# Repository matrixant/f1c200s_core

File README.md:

#f1c200s_core

> 已打板点灯验证，没有测试过稳定性，谨慎应用。

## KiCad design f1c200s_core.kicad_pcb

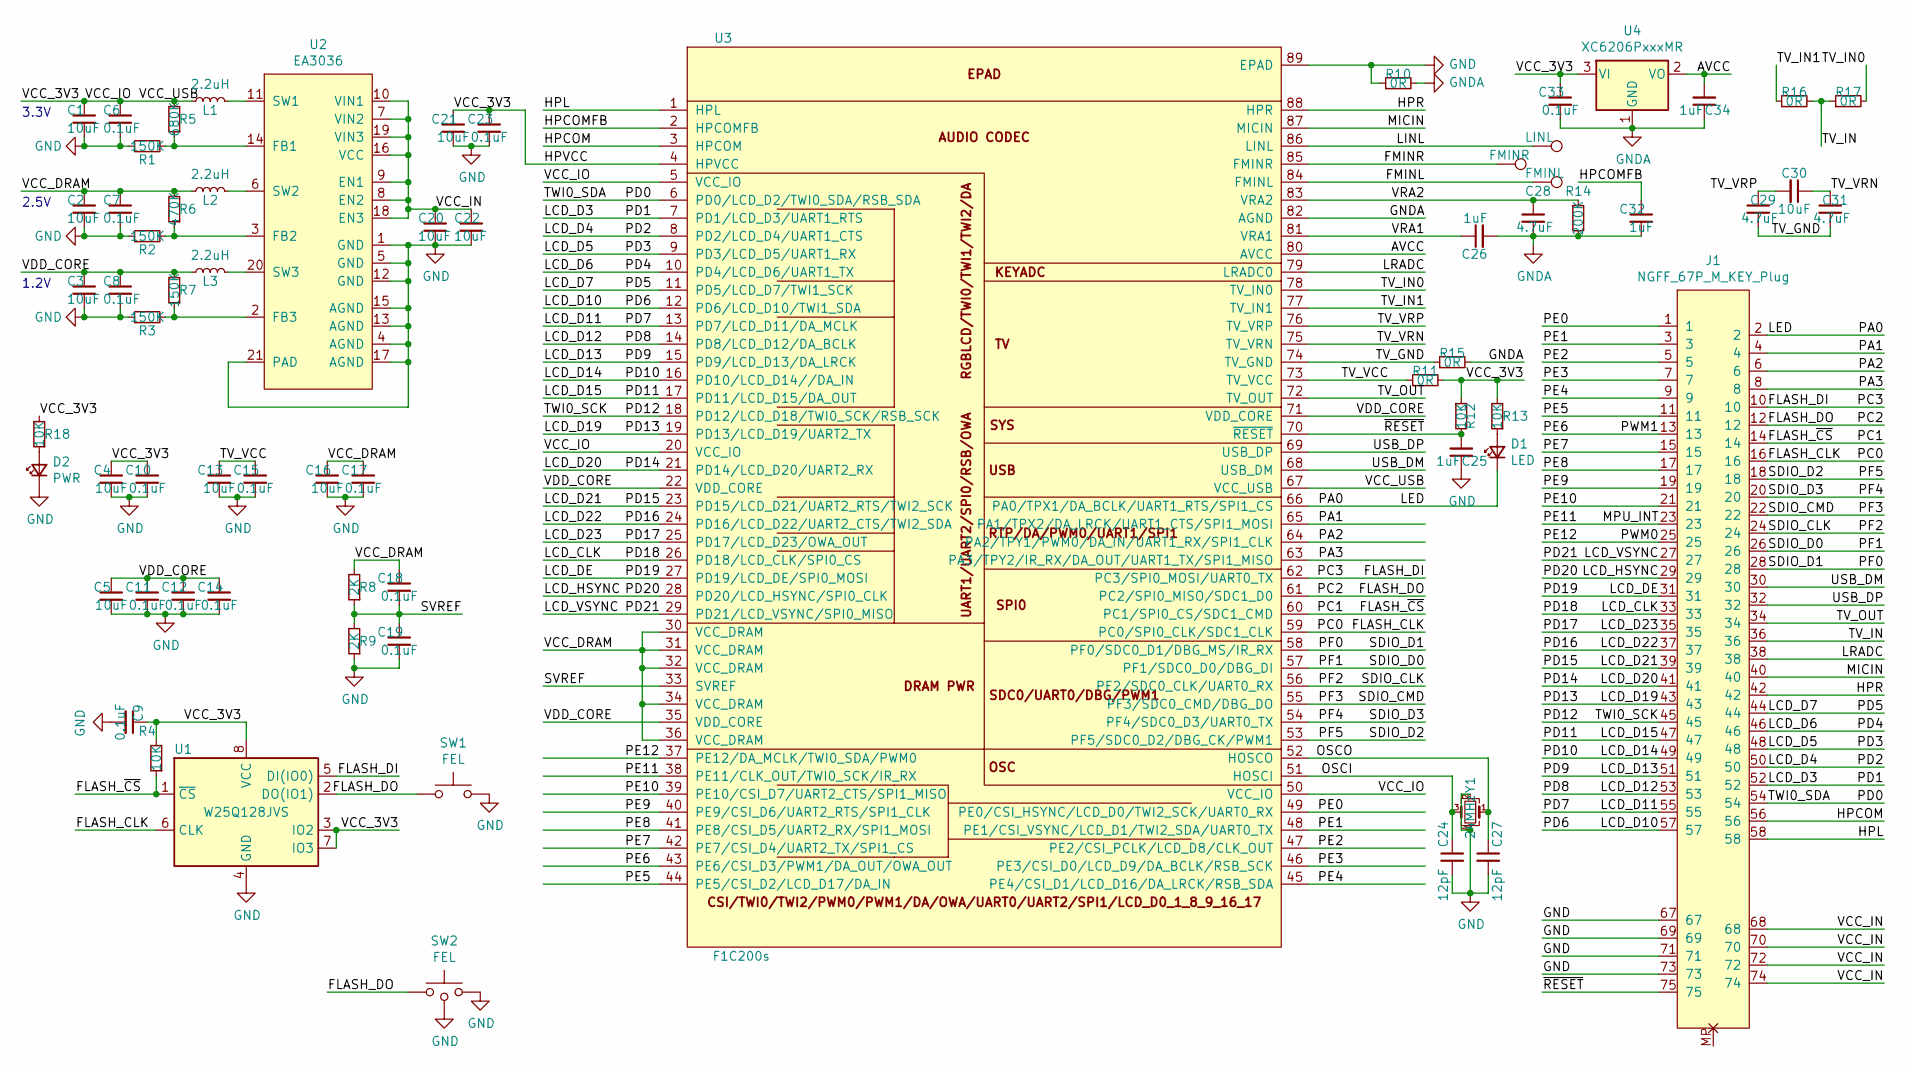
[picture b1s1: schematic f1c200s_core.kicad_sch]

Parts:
C1, C2, C3, C4, C5, C13, C16, C20, C21, C22, C30: 10uF; C_0402_1005Metric
C6, C7, C8, C9, C10, C11, C12, C14, C15, C17, C18, C19, C23, C33: 0.1uF; C_0402_1005Metric
C24, C27: 12pF; C_0402_1005Metric
C25, C26, C32, C34: 1uF; C_0402_1005Metric
C28, C29, C31: 4.7uF; C_0402_1005Metric
D1: LED; LED_0603_1608Metric
D2: PWR; LED_0603_1608Metric
J1: NGFF_67P_M_KEY_Plug; NGFF_2230_67P_P0.5_M_KEY_Plug
L1, L2, L3: 2.2uH; L_1008_2520Metric
R1, R2, R3, R7: 150K; R_0402_1005Metric
R4, R12, R13, R18: 10K; R_0402_1005Metric
R5: 680K; R_0402_1005Metric
R6: 470K; R_0402_1005Metric
R8, R9: 2K; R_0402_1005Metric
R10, R11, R15, R16, R17: 0R; R_0402_1005Metric
R14: 200K; R_0402_1005Metric
SW1: FEL; Key_Push_3.5x5x1.5_Side_4P
SW2: FEL; Key_Push_2x4x3.5_Side_4P
TP1: FMINR; TestPoint_Pad_D1.0mm
TP2: LINL; TestPoint_Pad_D1.0mm
TP3: FMINL; TestPoint_Pad_D1.0mm
U1: W25Q128JVS; WSON-8_8x6mm
U2: EA3036; QFN-20_EP_3x3_Pitch0.4mm_ThermalVias
U3: F1C200s; QFN-88_EP_10x10_Pitch0.4mm_Handsoldering
U4: XC6206PxxxMR; SOT-23
Y1: 24MHz; Crystal_SMD_3225-4Pin_3.2x2.5mm

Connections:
/AVCC: C34.2, U3.80 (AVCC), U4.2 (VO)
/FLASH_CLK: J1.16, U1.6 (CLK), U3.59 (PC0/SPI0_CLK/SDC1_CLK)
/FLASH_DI: J1.10, U1.5 (DI(IO0)), U3.62 (PC3/SPI0_MOSI/UART0_TX)
/FLASH_DO: J1.12, SW1.2, SW2.2, U1.2 (DO(IO1)), U3.61 (PC2/SPI0_MISO/SDC1_D0)
/FLASH_~CS: J1.14, R4.1, U1.1 (~CS), U3.60 (PC1/SPI0_CS/SDC1_CMD)
/FMINL: TP3.1, U3.84 (FMINL)
/FMINR: TP1.1, U3.85 (FMINR)
/HPCOM: J1.56, U3.3 (HPCOM)
/HPCOMFB: C32.1, U3.2 (HPCOMFB)
/HPL: J1.58, U3.1 (HPL)
/HPR: J1.42, U3.88 (HPR)
/HPVCC: C1.1, C4.1, C6.1, C9.1, C10.1, C21.1, C23.1, C33.1, L1.1, R4.2, R5.2, R11.2, R12.1, R13.2, R18.2, U1.3 (IO2), U1.7 (IO3), U1.8 (VCC), U3.4 (HPVCC), U3.5 (VCC_IO), U3.20 (VCC_IO), U3.50 (VCC_IO), U3.67 (VCC_USB), U4.3 (VI)
/LCD_CLK: J1.33, U3.26 (PD18/LCD_CLK/SPI0_CS)
/LCD_D3: J1.52, U3.7 (PD1/LCD_D3/UART1_RTS)
/LCD_D4: J1.50, U3.8 (PD2/LCD_D4/UART1_CTS)
/LCD_D5: J1.48, U3.9 (PD3/LCD_D5/UART1_RX)
/LCD_D6: J1.46, U3.10 (PD4/LCD_D6/UART1_TX)
/LCD_D7: J1.44, U3.11 (PD5/LCD_D7/TWI1_SCK)
/LCD_D10: J1.57, U3.12 (PD6/LCD_D10/TWI1_SDA)
/LCD_D11: J1.55, U3.13 (PD7/LCD_D11/DA_MCLK)
/LCD_D12: J1.53, U3.14 (PD8/LCD_D12/DA_BCLK)
/LCD_D13: J1.51, U3.15 (PD9/LCD_D13/DA_LRCK)
/LCD_D14: J1.49, U3.16 (PD10/LCD_D14//DA_IN)
/LCD_D15: J1.47, U3.17 (PD11/LCD_D15/DA_OUT)
/LCD_D19: J1.43, U3.19 (PD13/LCD_D19/UART2_TX)
/LCD_D20: J1.41, U3.21 (PD14/LCD_D20/UART2_RX)
/LCD_D21: J1.39, U3.23 (PD15/LCD_D21/UART2_RTS/TWI2_SCK)
/LCD_D22: J1.37, U3.24 (PD16/LCD_D22/UART2_CTS/TWI2_SDA)
/LCD_D23: J1.35, U3.25 (PD17/LCD_D23/OWA_OUT)
/LCD_DE: J1.31, U3.27 (PD19/LCD_DE/SPI0_MOSI)
/LCD_HSYNC: J1.29, U3.28 (PD20/LCD_HSYNC/SPI0_CLK)
/LCD_VSYNC: J1.27, U3.29 (PD21/LCD_VSYNC/SPI0_MISO)
/LED: D1.1 (K), J1.2, U3.66 (PA0/TPX1/DA_BCLK/UART1_RTS/SPI1_CS)
/LINL: TP2.1, U3.86 (LINL)
/LRADC: J1.38, U3.79 (LRADC0)
/MICIN: J1.40, U3.87 (MICIN)
/MPU_INT: J1.23, U3.38 (PE11/CLK_OUT/TWI0_SCK/IR_RX)
/OSCI: C24.1, U3.51 (HOSCI), Y1.3
/OSCO: C27.1, U3.52 (HOSCO), Y1.1
/PA1: J1.4, U3.65 (PA1/TPX2/DA_LRCK/UART1_CTS/SPI1_MOSI)
/PA2: J1.6, U3.64 (PA2/TPY1/PWM0/DA_IN/UART1_RX/SPI1_CLK)
/PA3: J1.8, U3.63 (PA3/TPY2/IR_RX/DA_OUT/UART1_TX/SPI1_MISO)
/PD0: J1.54, U3.6 (PD0/LCD_D2/TWI0_SDA/RSB_SDA)
/PD12: J1.45, U3.18 (PD12/LCD_D18/TWI0_SCK/RSB_SCK)
/PE0: J1.1, U3.49 (PE0/CSI_HSYNC/LCD_D0/TWI2_SCK/UART0_RX)
/PE1: J1.3, U3.48 (PE1/CSI_VSYNC/LCD_D1/TWI2_SDA/UART0_TX)
/PE2: J1.5, U3.47 (PE2/CSI_PCLK/LCD_D8/CLK_OUT)
/PE3: J1.7, U3.46 (PE3/CSI_D0/LCD_D9/DA_BCLK/RSB_SCK)
/PE4: J1.9, U3.45 (PE4/CSI_D1/LCD_D16/DA_LRCK/RSB_SDA)
/PE5: J1.11, U3.44 (PE5/CSI_D2/LCD_D17/DA_IN)
/PE6: J1.13, U3.43 (PE6/CSI_D3/PWM1/DA_OUT/OWA_OUT)
/PE7: J1.15, U3.42 (PE7/CSI_D4/UART2_TX/SPI1_CS)
/PE8: J1.17, U3.41 (PE8/CSI_D5/UART2_RX/SPI1_MOSI)
/PE9: J1.19, U3.40 (PE9/CSI_D6/UART2_RTS/SPI1_CLK)
/PE10: J1.21, U3.39 (PE10/CSI_D7/UART2_CTS/SPI1_MISO)
/PE12: J1.25, U3.37 (PE12/DA_MCLK/TWI0_SDA/PWM0)
/PF0: J1.28, U3.58 (PF0/SDC0_D1/DBG_MS/IR_RX)
/PF1: J1.26, U3.57 (PF1/SDC0_D0/DBG_DI)
/PF2: J1.24, U3.56 (PF2/SDC0_CLK/UART0_RX)
/PF3: J1.22, U3.55 (PF3/SDC0_CMD/DBG_DO)
/PF4: J1.20, U3.54 (PF4/SDC0_D3/UART0_TX)
/PF5: J1.18, U3.53 (PF5/SDC0_D2/DBG_CK/PWM1)
/SVREF: C18.2, C19.1, R8.1, R9.2, U3.33 (SVREF)
/TV_GND: C29.2, C31.2, R15.1, U3.74 (TV_GND)
/TV_IN: J1.36, R16.2, R17.1
/TV_IN0: R17.2, U3.78 (TV_IN0)
/TV_IN1: R16.1, U3.77 (TV_IN1)
/TV_OUT: J1.34, U3.72 (TV_OUT)
/TV_VCC: C13.1, C15.1, R11.1, U3.73 (TV_VCC)
/TV_VRN: C30.1, C31.1, U3.75 (TV_VRN)
/TV_VRP: C29.1, C30.2, U3.76 (TV_VRP)
/USB_DM: J1.30, U3.68 (USB_DM)
/USB_DP: J1.32, U3.69 (USB_DP)
/VCC_DRAM: C2.1, C7.1, C16.1, C17.1, C18.1, L2.1, R6.2, R8.2, U3.30 (VCC_DRAM), U3.31 (VCC_DRAM), U3.32 (VCC_DRAM), U3.34 (VCC_DRAM), U3.36 (VCC_DRAM)
/VCC_IN: C20.1, C22.1, J1.68, J1.70, J1.72, J1.74, U2.7 (VIN2), U2.8 (EN2), U2.9 (EN1), U2.10 (VIN1), U2.16 (VCC), U2.18 (EN3), U2.19 (VIN3)
/VDD_CORE: C3.1, C5.1, C8.1, C11.1, C12.1, C14.1, L3.1, R7.2, U3.22 (VDD_CORE), U3.35 (VDD_CORE), U3.71 (VDD_CORE)
/VRA1: C26.1, U3.81 (VRA1)
/VRA2: C28.1, R14.1, U3.83 (VRA2)
/~RESET: C25.2, J1.75, R12.2, U3.70 (~RESET)
GND: C1.2, C2.2, C3.2, C4.2, C5.2, C6.2, C7.2, C8.2, C9.2, C10.2, C11.2, C12.2, C13.2, C14.2, C15.2, C16.2, C17.2, C19.2, C20.2, C21.2, C22.2, C23.2, C24.2, C25.1, C27.2, D2.1 (K), J1.67, J1.69, J1.71, J1.73, R1.1, R2.1, R3.1, R9.1, R10.1, SW1.1, SW2.1, SW2.3 (GND), U1.4 (GND), U2.1 (GND), U2.4 (AGND), U2.5 (GND), U2.12 (GND), U2.13 (AGND), U2.15 (AGND), U2.17 (AGND), U2.21 (PAD), U3.89 (EPAD), Y1.2, Y1.4
GNDA: C26.2, C28.2, C32.2, C33.2, C34.1, R10.2, R14.2, R15.2, U3.82 (AGND), U4.1 (GND)
unnamed: D1.2 (A), R13.1
unnamed: D2.2 (A), R18.1
unnamed: L1.2, U2.11 (SW1)
unnamed: L2.2, U2.6 (SW2)
unnamed: L3.2, U2.20 (SW3)
unnamed: R1.2, R5.1, U2.14 (FB1)
unnamed: R2.2, R6.1, U2.3 (FB2)
unnamed: R3.2, R7.1, U2.2 (FB3)

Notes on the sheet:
2.5V
3.3V
1.2V

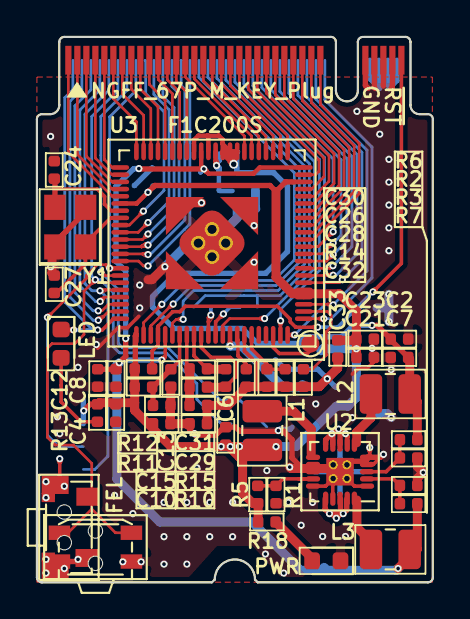
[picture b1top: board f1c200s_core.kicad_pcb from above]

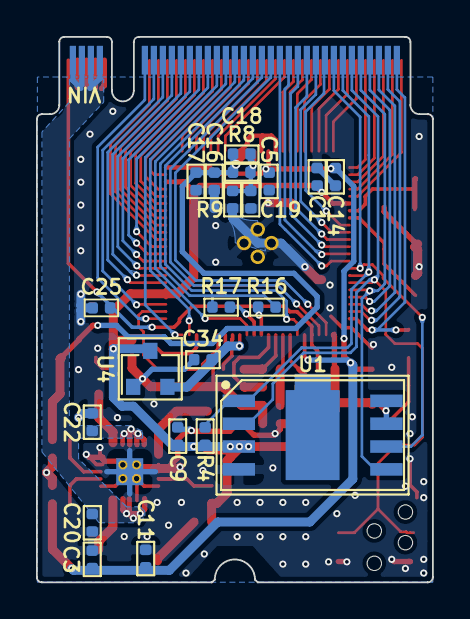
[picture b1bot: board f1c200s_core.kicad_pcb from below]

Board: 2 copper layers, 22.0 x 30.3 mm, 66 parts (21 on the bottom side), 87 nets.

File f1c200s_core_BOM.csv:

"Comment","Description","Designator","Footprint","LibRef","Pins","Quantity","PartNumber","url",
"12pF","desc","C27,C24,","C_0402_1005Metric","libref","2","2","","",
"10uF","desc","C30,C21,C13,C4,C2,","C_0402_1005Metric","libref","2","5","","",
"4.7uF","desc","C31,C29,C28,","C_0402_1005Metric","libref","2","3","","",
"1uF","desc","C32,C26,","C_0402_1005Metric","libref","2","2","","",
"0.1uF","desc","C33,C23,C15,C12,C10,C8,C7,C6,","C_0402_1005Metric","libref","2","8","","",
"LED","desc","D1,","LED_0603_1608Metric","libref","2","1","","",
"PWR","desc","D2,","LED_0603_1608Metric","libref","2","1","","",
"NGFF_67P_M_KEY_Plug","desc","J1,","NGFF_2230_67P_P0.5_M_KEY_Plug","libref","67","1","","",
"2.2uH","desc","L3,L2,L1,","L_1008_2520Metric","libref","2","3","","",
"200K","desc","R14,","R_0402_1005Metric","libref","2","1","","",
"0R","desc","R15,R11,R10,","R_0402_1005Metric","libref","2","3","","",
"10K","desc","R18,R13,R12,","R_0402_1005Metric","libref","2","3","","",
"680K","desc","R5,","R_0402_1005Metric","libref","2","1","","",
"470K","desc","R6,","R_0402_1005Metric","libref","2","1","","",
"150K","desc","R7,R3,R2,R1,","R_0402_1005Metric","libref","2","4","","",
"LINL","desc","TP2,","TestPoint_Pad_D1.0mm","libref","1","1","","",
"24MHz","desc","Y1,","Crystal_SMD_3225-4Pin_3.2x2.5mm","libref","4","1","","",
"0.1uF","desc","C19,C18,C17,C14,C11,C9,","C_0402_1005Metric","libref","2","6","","",
"10uF","desc","C22,C20,C16,C5,C3,C1,","C_0402_1005Metric","libref","2","6","","",
"1uF","desc","C34,C25,","C_0402_1005Metric","libref","2","2","","",
"0R","desc","R17,R16,","R_0402_1005Metric","libref","2","2","","",
"10K","desc","R4,","R_0402_1005Metric","libref","2","1","","",
"2K","desc","R9,R8,","R_0402_1005Metric","libref","2","2","","",
"W25Q128JVS","desc","U1,","WSON-8_8x6mm","libref","10","1","","",
"XC6206PxxxMR","desc","U4,","SOT-23","libref","3","1","","",
"Through Hole Items ",
"FEL","desc","SW1,","Key_Push_3.5x5x1.5_Side_4P","libref","6","1","","",
"FEL","desc","SW2,","Key_Push_2x4x3.5_Side_4P","libref","8","1","","",
"EA3036","desc","U2,","QFN-20_EP_3x3_Pitch0.4mm_ThermalVias","libref","29","1","","",
"F1C200s","desc","U3,","QFN-88_EP_10x10_Pitch0.4mm_Handsoldering","libref","97","1","","",

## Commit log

2021-12-30 add pcb picture
2021-12-30 Save as KiCad 6 project
